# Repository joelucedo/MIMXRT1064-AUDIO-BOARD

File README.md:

# MIMXRT1064 MCU BOARD

## WHAT ?
M7 MCU + SDRAM + FLASH + SD
</br>
## STATUS
Work in progress.
</br>
## SPECS
#### MCU : MIMXRT1064CVL5B 
* ***Cores*** : 1 x ARM Cortex M7 (32KB L1 Cache - FPU)
* ***Clock frequency*** : 528 MHz  
* ***On chip Flash*** : 4MB  
* ***On chip RAM*** : 1MB
* ***USB*** : Two USB 2.0 HS OTG controllers with integrated PHY interfaces
#### SDRAM : IS42S16160J-6BLI
* ***Memory Size*** : 256Mb
* ***Data Bus Width*** : 16 Bit
* ***Maximum clock frequency*** : 166MHz
#### QSPI Flash : IS25WP064A-JBLE
* ***Memory Size*** : 64Mbit
* ***Data Bus Width*** : 8 Bit
* ***Maximum clock frequency*** : 133MHz
#### SD Memory Card Socket
* ***Capacity*** : Up to 2TB SDHX card
* ***Data transfer rate*** : Up to 104 MB/s (UHS-I SDR104)

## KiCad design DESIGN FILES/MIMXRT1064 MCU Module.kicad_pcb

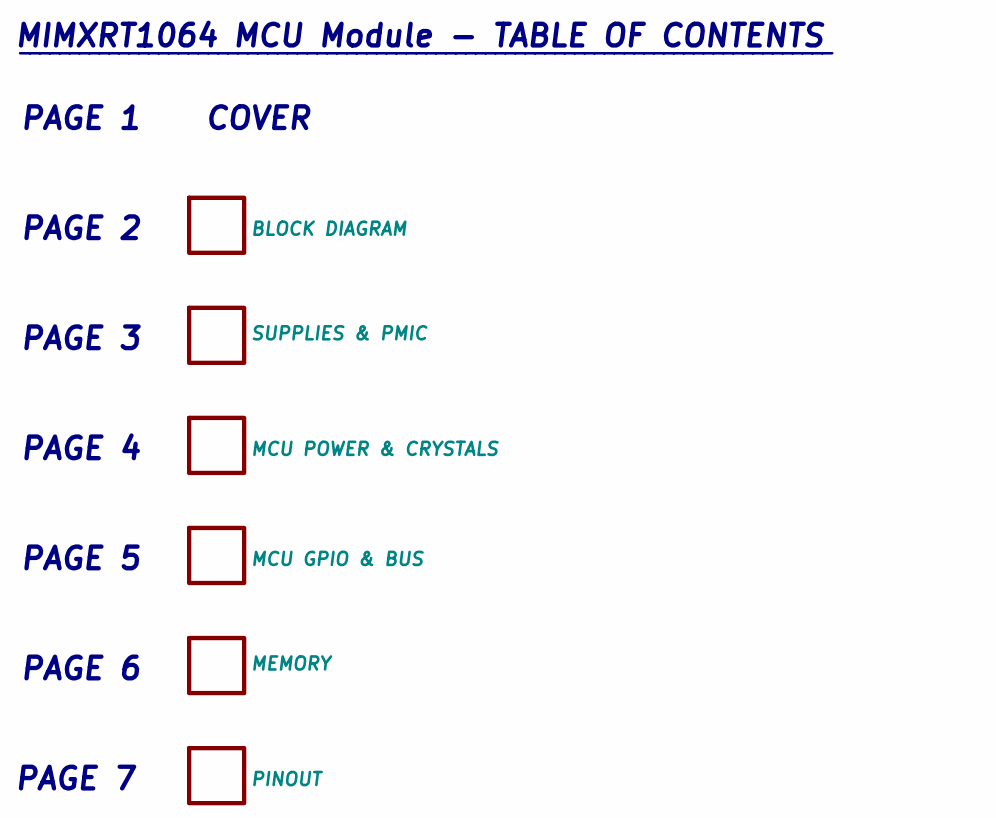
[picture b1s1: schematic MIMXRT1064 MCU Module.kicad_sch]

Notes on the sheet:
MIMXRT1064 MCU Module - TABLE OF CONTENTS
PAGE 6
PAGE 3
PAGE 4
PAGE 1 COVER
PAGE 2
PAGE 5
__________________________________________________________________________________
PAGE 7

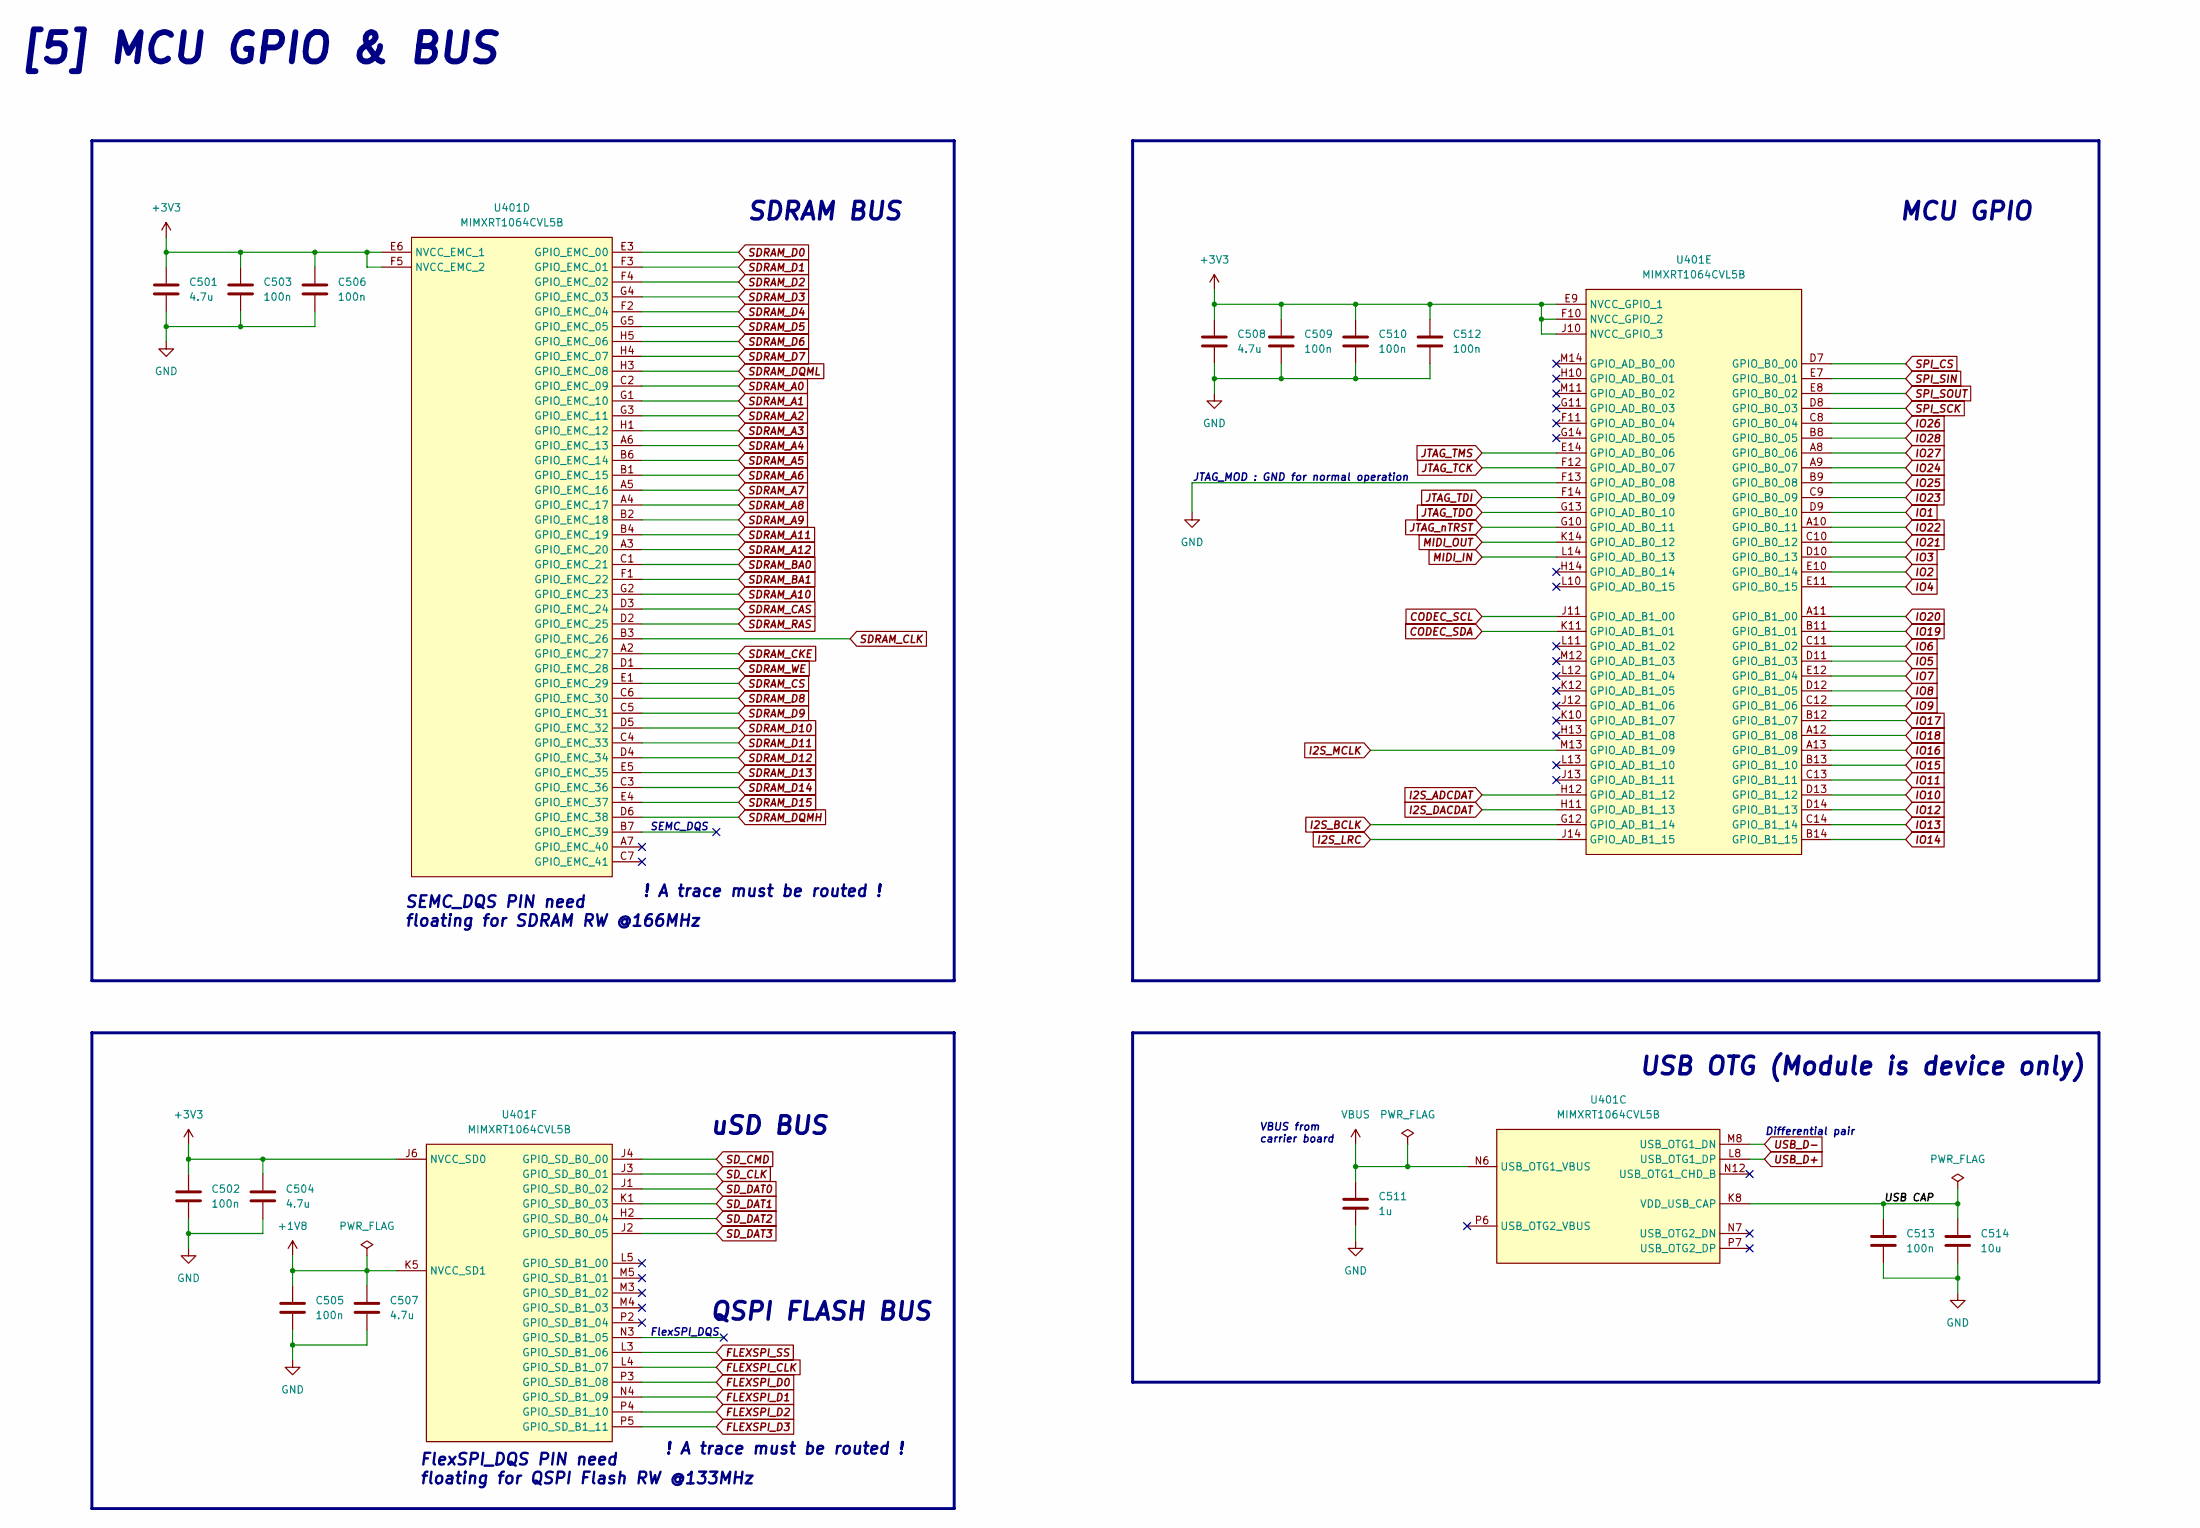
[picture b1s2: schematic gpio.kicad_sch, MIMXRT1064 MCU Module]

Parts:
C501, C504, C507, C508: 4.7u; 0402_CL05A475MP5NRNC
C502, C503, C505, C506, C509, C510, C512, C513: 100n; 0402_CL05B104KB54PNC
C511: 1u; 0402_CL05A105KA5NQNC
C514: 10u; 0603_CL10A106KP8NNNC
U401: MIMXRT1064CVL5B

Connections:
+1V8: C505.1, C507.1, U401.K5 (NVCC_SD1); also elsewhere on the board
+3V3: C501.1, C502.1, C503.1, C504.1, C506.1, C508.1, C509.1, C510.1, C512.1, U401.E6 (NVCC_EMC_1), U401.E9 (NVCC_GPIO_1), U401.F5 (NVCC_EMC_2), U401.F10 (NVCC_GPIO_2), U401.J6 (NVCC_SD0), U401.J10 (NVCC_GPIO_3); also elsewhere on the board
/MCU GPIO & BUS/USB CAP: C513.1, C514.1, U401.K8 (VDD_USB_CAP)
CODEC_SCL: U401.J11 (GPIO_AD_B1_00); also elsewhere on the board
CODEC_SDA: U401.K11 (GPIO_AD_B1_01); also elsewhere on the board
FLEXSPI_CLK: U401.L4 (GPIO_SD_B1_07); also elsewhere on the board
FLEXSPI_D0: U401.P3 (GPIO_SD_B1_08); also elsewhere on the board
FLEXSPI_D1: U401.N4 (GPIO_SD_B1_09); also elsewhere on the board
FLEXSPI_D2: U401.P4 (GPIO_SD_B1_10); also elsewhere on the board
FLEXSPI_D3: U401.P5 (GPIO_SD_B1_11); also elsewhere on the board
FLEXSPI_SS: U401.L3 (GPIO_SD_B1_06); also elsewhere on the board
GND: C501.2, C502.2, C503.2, C504.2, C505.2, C506.2, C507.2, C508.2, C509.2, C510.2, C511.2, C512.2, C513.2, C514.2, U401.F13 (GPIO_AD_B0_08); also elsewhere on the board
I2S_ADCDAT: U401.H12 (GPIO_AD_B1_12); also elsewhere on the board
I2S_BCLK: U401.G12 (GPIO_AD_B1_14); also elsewhere on the board
I2S_DACDAT: U401.H11 (GPIO_AD_B1_13); also elsewhere on the board
I2S_LRC: U401.J14 (GPIO_AD_B1_15); also elsewhere on the board
I2S_MCLK: U401.M13 (GPIO_AD_B1_09); also elsewhere on the board
IO1: U401.D9 (GPIO_B0_10); also elsewhere on the board
IO2: U401.E10 (GPIO_B0_14); also elsewhere on the board
IO3: U401.D10 (GPIO_B0_13); also elsewhere on the board
IO4: U401.E11 (GPIO_B0_15); also elsewhere on the board
IO5: U401.D11 (GPIO_B1_03); also elsewhere on the board
IO6: U401.C11 (GPIO_B1_02); also elsewhere on the board
IO7: U401.E12 (GPIO_B1_04); also elsewhere on the board
IO8: U401.D12 (GPIO_B1_05); also elsewhere on the board
IO9: U401.C12 (GPIO_B1_06); also elsewhere on the board
IO10: U401.D13 (GPIO_B1_12); also elsewhere on the board
IO11: U401.C13 (GPIO_B1_11); also elsewhere on the board
IO12: U401.D14 (GPIO_B1_13); also elsewhere on the board
IO13: U401.C14 (GPIO_B1_14); also elsewhere on the board
IO14: U401.B14 (GPIO_B1_15); also elsewhere on the board
IO15: U401.B13 (GPIO_B1_10); also elsewhere on the board
IO16: U401.A13 (GPIO_B1_09); also elsewhere on the board
IO17: U401.B12 (GPIO_B1_07); also elsewhere on the board
IO18: U401.A12 (GPIO_B1_08); also elsewhere on the board
IO19: U401.B11 (GPIO_B1_01); also elsewhere on the board
IO20: U401.A11 (GPIO_B1_00); also elsewhere on the board
IO21: U401.C10 (GPIO_B0_12); also elsewhere on the board
IO22: U401.A10 (GPIO_B0_11); also elsewhere on the board
IO23: U401.C9 (GPIO_B0_09); also elsewhere on the board
IO24: U401.A9 (GPIO_B0_07); also elsewhere on the board
IO25: U401.B9 (GPIO_B0_08); also elsewhere on the board
IO26: U401.C8 (GPIO_B0_04); also elsewhere on the board
IO27: U401.A8 (GPIO_B0_06); also elsewhere on the board
IO28: U401.B8 (GPIO_B0_05); also elsewhere on the board
JTAG_TCK: U401.F12 (GPIO_AD_B0_07); also elsewhere on the board
JTAG_TDI: U401.F14 (GPIO_AD_B0_09); also elsewhere on the board
JTAG_TDO: U401.G13 (GPIO_AD_B0_10); also elsewhere on the board
JTAG_TMS: U401.E14 (GPIO_AD_B0_06); also elsewhere on the board
JTAG_nTRST: U401.G10 (GPIO_AD_B0_11); also elsewhere on the board
MIDI_IN: U401.L14 (GPIO_AD_B0_13); also elsewhere on the board
MIDI_OUT: U401.K14 (GPIO_AD_B0_12); also elsewhere on the board
SDRAM_A0: U401.C2 (GPIO_EMC_09); also elsewhere on the board
SDRAM_A1: U401.G1 (GPIO_EMC_10); also elsewhere on the board
SDRAM_A2: U401.G3 (GPIO_EMC_11); also elsewhere on the board
SDRAM_A3: U401.H1 (GPIO_EMC_12); also elsewhere on the board
SDRAM_A4: U401.A6 (GPIO_EMC_13); also elsewhere on the board
SDRAM_A5: U401.B6 (GPIO_EMC_14); also elsewhere on the board
SDRAM_A6: U401.B1 (GPIO_EMC_15); also elsewhere on the board
SDRAM_A7: U401.A5 (GPIO_EMC_16); also elsewhere on the board
SDRAM_A8: U401.A4 (GPIO_EMC_17); also elsewhere on the board
SDRAM_A9: U401.B2 (GPIO_EMC_18); also elsewhere on the board
SDRAM_A10: U401.G2 (GPIO_EMC_23); also elsewhere on the board
SDRAM_A11: U401.B4 (GPIO_EMC_19); also elsewhere on the board
SDRAM_A12: U401.A3 (GPIO_EMC_20); also elsewhere on the board
SDRAM_BA0: U401.C1 (GPIO_EMC_21); also elsewhere on the board
SDRAM_BA1: U401.F1 (GPIO_EMC_22); also elsewhere on the board
SDRAM_CAS: U401.D3 (GPIO_EMC_24); also elsewhere on the board
SDRAM_CKE: U401.A2 (GPIO_EMC_27); also elsewhere on the board
SDRAM_CLK: U401.B3 (GPIO_EMC_26); also elsewhere on the board
SDRAM_CS: U401.E1 (GPIO_EMC_29); also elsewhere on the board
SDRAM_D0: U401.E3 (GPIO_EMC_00); also elsewhere on the board
SDRAM_D1: U401.F3 (GPIO_EMC_01); also elsewhere on the board
SDRAM_D2: U401.F4 (GPIO_EMC_02); also elsewhere on the board
SDRAM_D3: U401.G4 (GPIO_EMC_03); also elsewhere on the board
SDRAM_D4: U401.F2 (GPIO_EMC_04); also elsewhere on the board
SDRAM_D5: U401.G5 (GPIO_EMC_05); also elsewhere on the board
SDRAM_D6: U401.H5 (GPIO_EMC_06); also elsewhere on the board
SDRAM_D7: U401.H4 (GPIO_EMC_07); also elsewhere on the board
SDRAM_D8: U401.C6 (GPIO_EMC_30); also elsewhere on the board
SDRAM_D9: U401.C5 (GPIO_EMC_31); also elsewhere on the board
SDRAM_D10: U401.D5 (GPIO_EMC_32); also elsewhere on the board
SDRAM_D11: U401.C4 (GPIO_EMC_33); also elsewhere on the board
SDRAM_D12: U401.D4 (GPIO_EMC_34); also elsewhere on the board
SDRAM_D13: U401.E5 (GPIO_EMC_35); also elsewhere on the board
SDRAM_D14: U401.C3 (GPIO_EMC_36); also elsewhere on the board
SDRAM_D15: U401.E4 (GPIO_EMC_37); also elsewhere on the board
SDRAM_DQMH: U401.D6 (GPIO_EMC_38); also elsewhere on the board
SDRAM_DQML: U401.H3 (GPIO_EMC_08); also elsewhere on the board
SDRAM_RAS: U401.D2 (GPIO_EMC_25); also elsewhere on the board
SDRAM_WE: U401.D1 (GPIO_EMC_28); also elsewhere on the board
SD_CLK: U401.J3 (GPIO_SD_B0_01); also elsewhere on the board
SD_CMD: U401.J4 (GPIO_SD_B0_00); also elsewhere on the board
SD_DAT0: U401.J1 (GPIO_SD_B0_02); also elsewhere on the board
SD_DAT1: U401.K1 (GPIO_SD_B0_03); also elsewhere on the board
SD_DAT2: U401.H2 (GPIO_SD_B0_04); also elsewhere on the board
SD_DAT3: U401.J2 (GPIO_SD_B0_05); also elsewhere on the board
SPI_CS: U401.D7 (GPIO_B0_00); also elsewhere on the board
SPI_SCK: U401.D8 (GPIO_B0_03); also elsewhere on the board
SPI_SIN: U401.E7 (GPIO_B0_01); also elsewhere on the board
SPI_SOUT: U401.E8 (GPIO_B0_02); also elsewhere on the board
USB_D+: U401.L8 (USB_OTG1_DP); also elsewhere on the board
USB_D-: U401.M8 (USB_OTG1_DN); also elsewhere on the board
VBUS: C511.1, U401.N6 (USB_OTG1_VBUS); also elsewhere on the board

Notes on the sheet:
QSPI FLASH BUS
uSD BUS
SDRAM BUS
Differential pair
USB OTG (Module is device only)
FlexSPI_DQS
[5] MCU GPIO & BUS
VBUS from carrier board
SEMC_DQS
MCU GPIO
! A trace must be routed !
FlexSPI_DQS PIN need floating for QSPI Flash RW @133MHz
SEMC_DQS PIN need floating for SDRAM RW @166MHz
JTAG_MOD : GND for normal operation

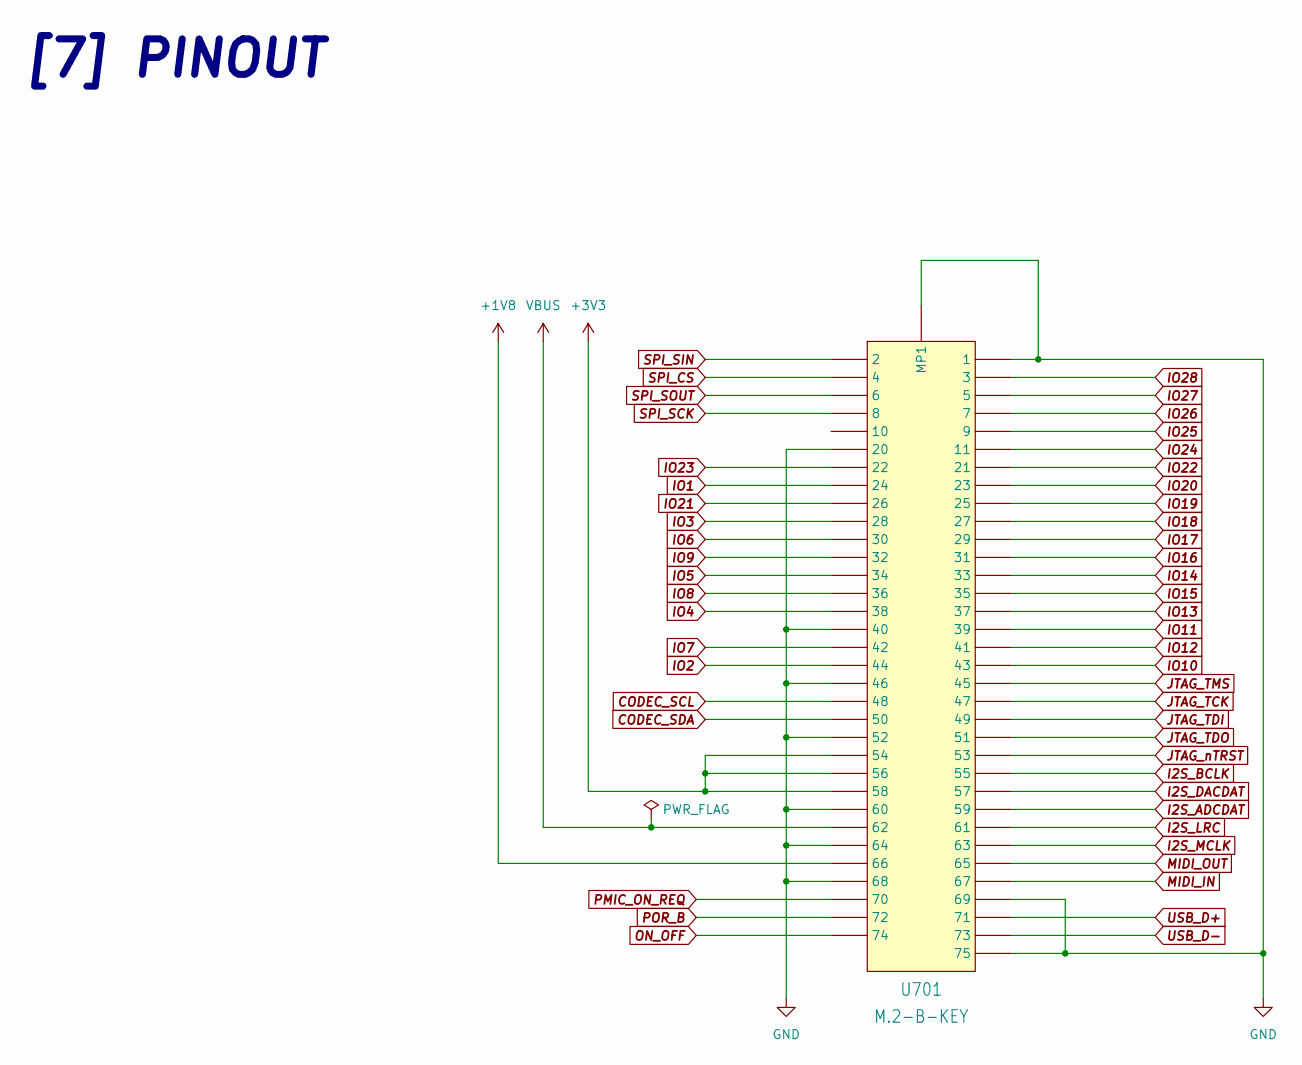
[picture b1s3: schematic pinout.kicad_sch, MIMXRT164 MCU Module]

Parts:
U701: M.2-B-KEY

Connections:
+1V8: U701.P$66 (66); also elsewhere on the board
+3V3: U701.P$54 (54), U701.P$56 (56), U701.P$58 (58); also elsewhere on the board
CODEC_SCL: U701.P$48 (48); also elsewhere on the board
CODEC_SDA: U701.P$50 (50); also elsewhere on the board
GND: U701.MOUNTING-HOLE (MP1), U701.P$1 (1), U701.P$20 (20), U701.P$40 (40), U701.P$46 (46), U701.P$52 (52), U701.P$60 (60), U701.P$64 (64), U701.P$68 (68), U701.P$69 (69), U701.P$75 (75); also elsewhere on the board
I2S_ADCDAT: U701.P$59 (59); also elsewhere on the board
I2S_BCLK: U701.P$55 (55); also elsewhere on the board
I2S_DACDAT: U701.P$57 (57); also elsewhere on the board
I2S_LRC: U701.P$61 (61); also elsewhere on the board
I2S_MCLK: U701.P$63 (63); also elsewhere on the board
IO1: U701.P$24 (24); also elsewhere on the board
IO2: U701.P$44 (44); also elsewhere on the board
IO3: U701.P$28 (28); also elsewhere on the board
IO4: U701.P$38 (38); also elsewhere on the board
IO5: U701.P$34 (34); also elsewhere on the board
IO6: U701.P$30 (30); also elsewhere on the board
IO7: U701.P$42 (42); also elsewhere on the board
IO8: U701.P$36 (36); also elsewhere on the board
IO9: U701.P$32 (32); also elsewhere on the board
IO10: U701.P$43 (43); also elsewhere on the board
IO11: U701.P$39 (39); also elsewhere on the board
IO12: U701.P$41 (41); also elsewhere on the board
IO13: U701.P$37 (37); also elsewhere on the board
IO14: U701.P$33 (33); also elsewhere on the board
IO15: U701.P$35 (35); also elsewhere on the board
IO16: U701.P$31 (31); also elsewhere on the board
IO17: U701.P$29 (29); also elsewhere on the board
IO18: U701.P$27 (27); also elsewhere on the board
IO19: U701.P$25 (25); also elsewhere on the board
IO20: U701.P$23 (23); also elsewhere on the board
IO21: U701.P$26 (26); also elsewhere on the board
IO22: U701.P$21 (21); also elsewhere on the board
IO23: U701.P$22 (22); also elsewhere on the board
IO24: U701.P$11 (11); also elsewhere on the board
IO25: U701.P$9 (9); also elsewhere on the board
IO26: U701.P$7 (7); also elsewhere on the board
IO27: U701.P$5 (5); also elsewhere on the board
IO28: U701.P$3 (3); also elsewhere on the board
JTAG_TCK: U701.P$47 (47); also elsewhere on the board
JTAG_TDI: U701.P$49 (49); also elsewhere on the board
JTAG_TDO: U701.P$51 (51); also elsewhere on the board
JTAG_TMS: U701.P$45 (45); also elsewhere on the board
JTAG_nTRST: U701.P$53 (53); also elsewhere on the board
MIDI_IN: U701.P$67 (67); also elsewhere on the board
MIDI_OUT: U701.P$65 (65); also elsewhere on the board
ON_OFF: U701.P$74 (74); also elsewhere on the board
PMIC_ON_REQ: U701.P$70 (70); also elsewhere on the board
POR_B: U701.P$72 (72); also elsewhere on the board
SPI_CS: U701.P$4 (4); also elsewhere on the board
SPI_SCK: U701.P$8 (8); also elsewhere on the board
SPI_SIN: U701.P$2 (2); also elsewhere on the board
SPI_SOUT: U701.P$6 (6); also elsewhere on the board
USB_D+: U701.P$71 (71); also elsewhere on the board
USB_D-: U701.P$73 (73); also elsewhere on the board
VBUS: U701.P$62 (62); also elsewhere on the board

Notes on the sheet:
[7] PINOUT

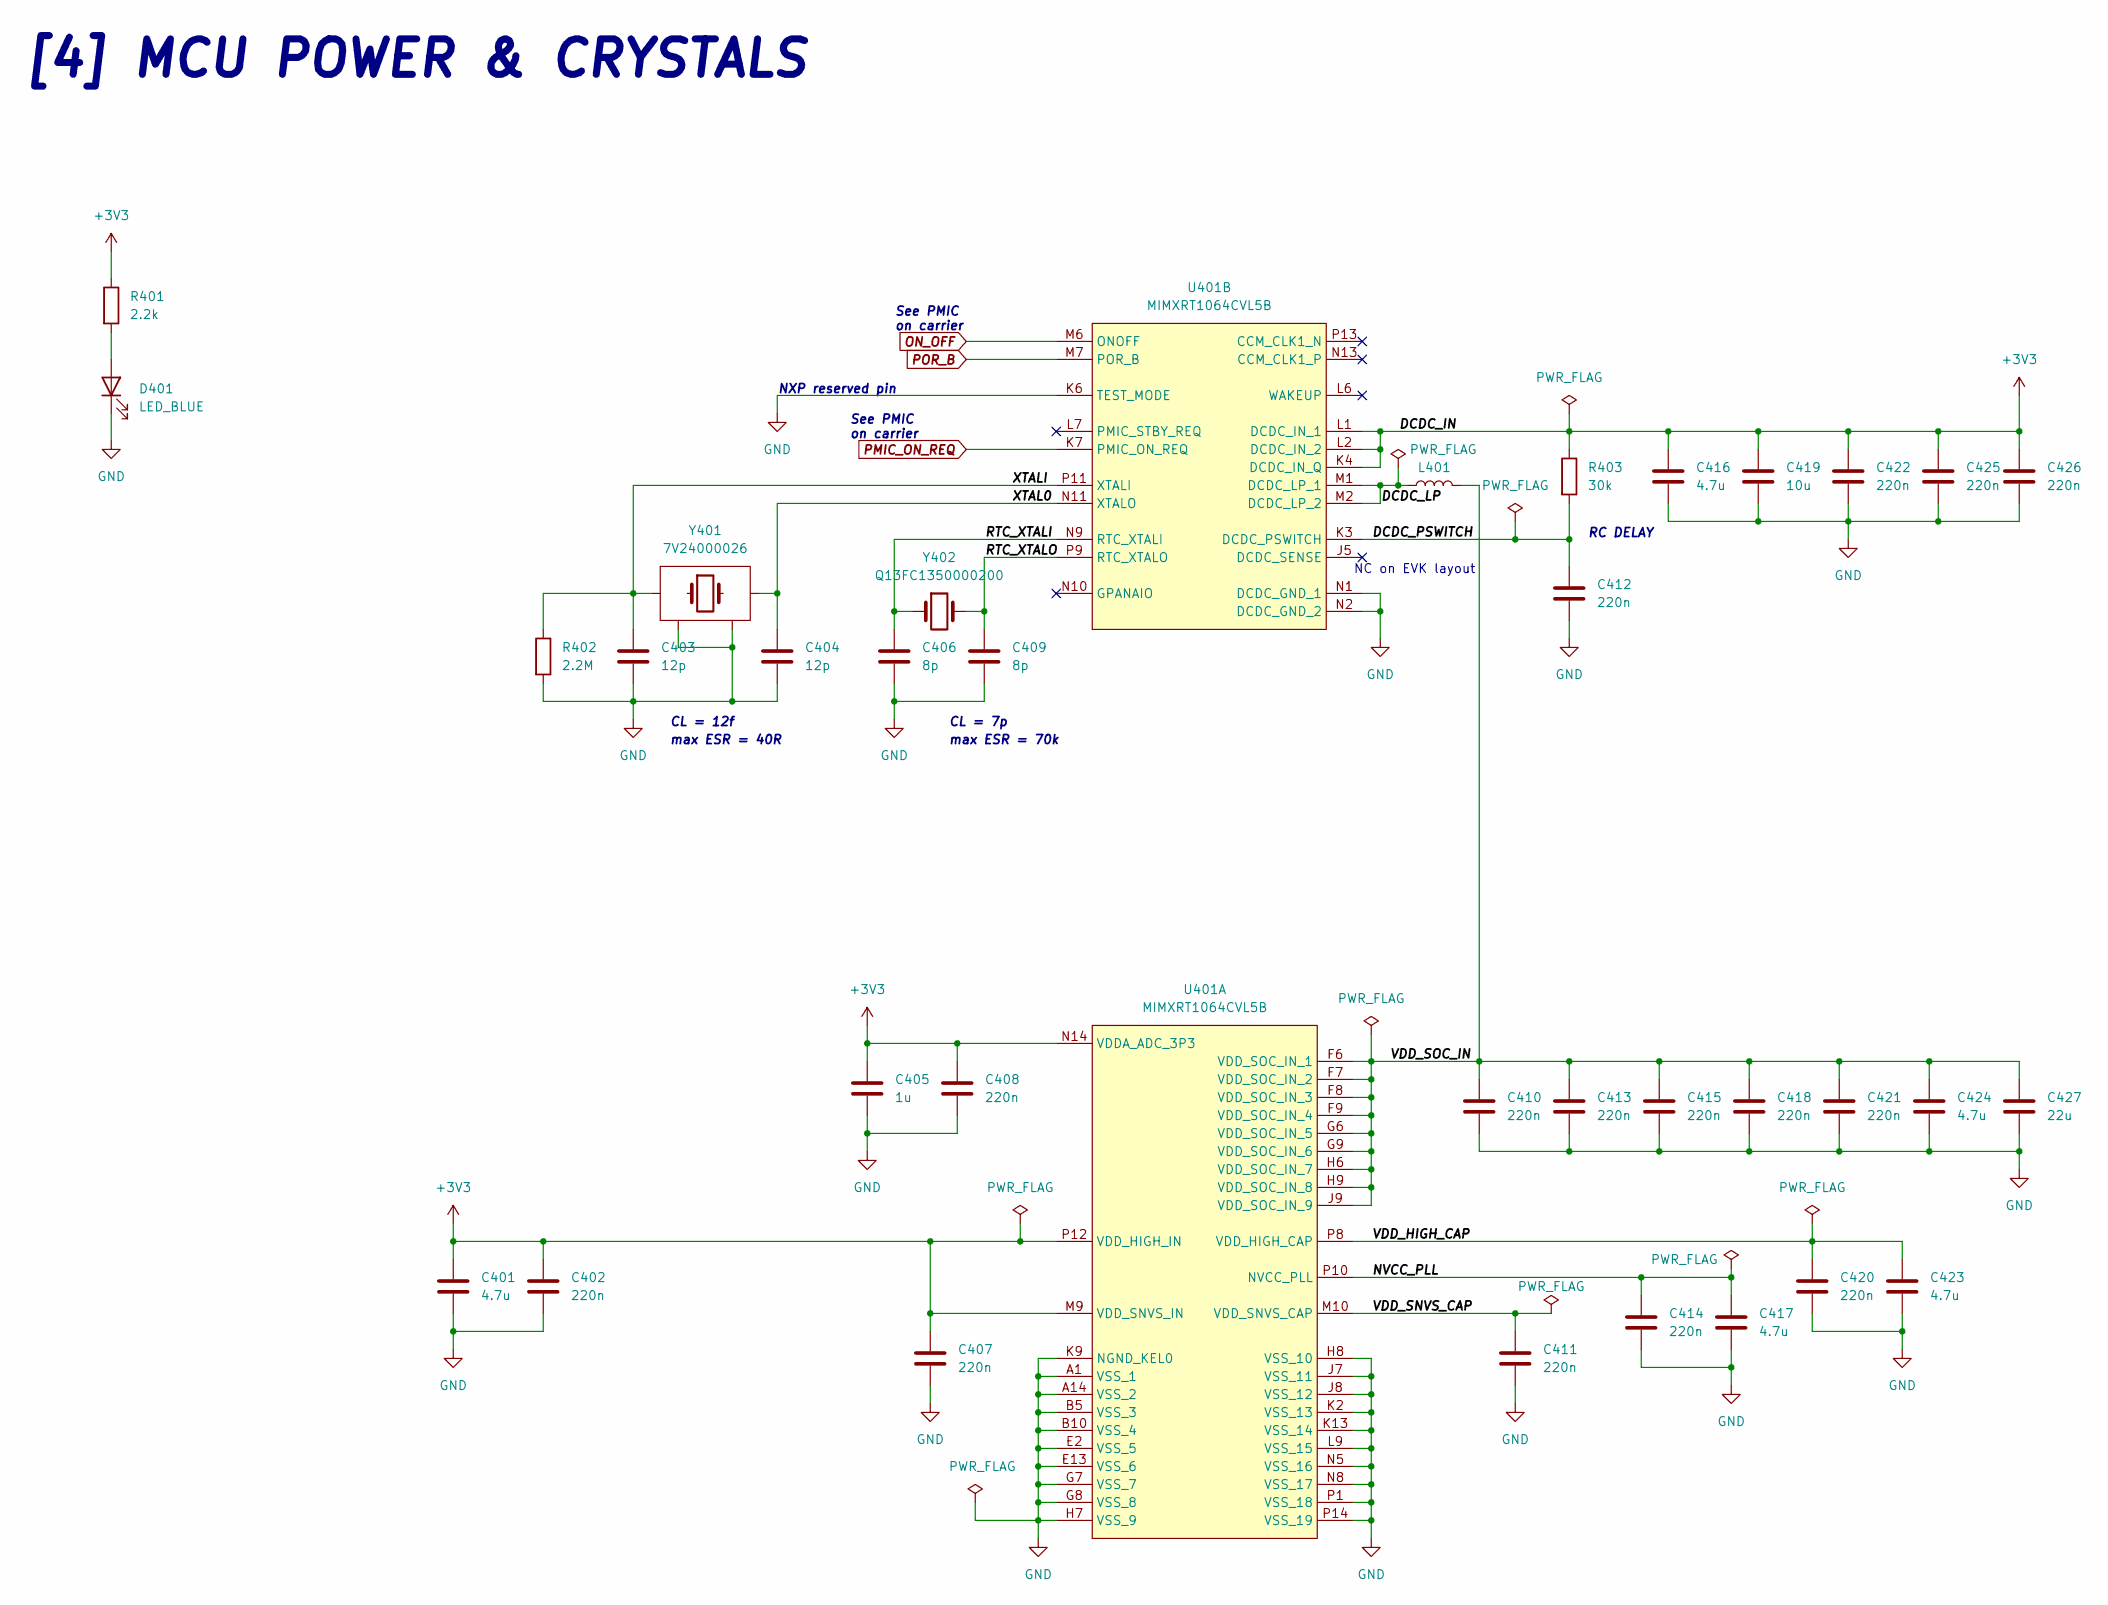
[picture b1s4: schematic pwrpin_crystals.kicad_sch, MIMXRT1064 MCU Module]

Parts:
C401, C416, C417, C423, C424: 4.7u; 0402_CL05A475MP5NRNC
C402, C407, C408, C410, C411, C412, C413, C414, C415, C418, C420, C421, C422, C425, C426: 220n; 0402_CL05B224KO5NNNC
C403, C404: 12p; CL10C120JB81PNC
C405: 1u; 0402_CL05A105KA5NQNC
C406, C409: 8p; CL10C080DB81PNC
C419: 10u; 0603_CL10A106KP8NNNC
C427: 22u; 0603_CL10A226MQ8NRNC
D401: LED_BLUE; 19-218_BHC-ZL1M2QY_3T
L401: VLS4012ET-4R7M
R401: 2.2k; 0603WAF2201T5E
R402: 2.2M; 0402WGJ0225TCE
R403: 30k; AF0402FR-0730KL
U401: MIMXRT1064CVL5B
Y401: 7V24000026
Y402: Q13FC1350000200

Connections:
+3V3: C401.1, C402.1, C405.1, C407.1, C408.1, C416.1, C419.1, C422.1, C425.1, C426.1, R401.1, R403.1, U401.K4 (DCDC_IN_Q), U401.L1 (DCDC_IN_1), U401.L2 (DCDC_IN_2), U401.M9 (VDD_SNVS_IN), U401.N14 (VDDA_ADC_3P3), U401.P12 (VDD_HIGH_IN); also elsewhere on the board
/MCU POWER & CRYSTALS/DCDC_LP: L401.1, U401.M1 (DCDC_LP_1), U401.M2 (DCDC_LP_2)
/MCU POWER & CRYSTALS/DCDC_PSWITCH: C412.1, R403.2, U401.K3 (DCDC_PSWITCH)
/MCU POWER & CRYSTALS/NVCC_PLL: C414.1, C417.1, U401.P10 (NVCC_PLL)
/MCU POWER & CRYSTALS/RTC_XTALI: C406.1, U401.N9 (RTC_XTALI), Y402.1
/MCU POWER & CRYSTALS/RTC_XTALO: C409.1, U401.P9 (RTC_XTALO), Y402.2
/MCU POWER & CRYSTALS/VDD_HIGH_CAP: C420.1, C423.1, U401.P8 (VDD_HIGH_CAP)
/MCU POWER & CRYSTALS/VDD_SNVS_CAP: C411.1, U401.M10 (VDD_SNVS_CAP)
/MCU POWER & CRYSTALS/VDD_SOC_IN: C410.1, C413.1, C415.1, C418.1, C421.1, C424.1, C427.1, L401.2, U401.F6 (VDD_SOC_IN_1), U401.F7 (VDD_SOC_IN_2), U401.F8 (VDD_SOC_IN_3), U401.F9 (VDD_SOC_IN_4), U401.G6 (VDD_SOC_IN_5), U401.G9 (VDD_SOC_IN_6), U401.H6 (VDD_SOC_IN_7), U401.H9 (VDD_SOC_IN_8), U401.J9 (VDD_SOC_IN_9)
/MCU POWER & CRYSTALS/XTAL0: C404.1, U401.N11 (XTALO), Y401.3
/MCU POWER & CRYSTALS/XTALI: C403.1, R402.1, U401.P11 (XTALI), Y401.1
GND: C401.2, C402.2, C403.2, C404.2, C405.2, C406.2, C407.2, C408.2, C409.2, C410.2, C411.2, C412.2, C413.2, C414.2, C415.2, C416.2, C417.2, C418.2, C419.2, C420.2, C421.2, C422.2, C423.2, C424.2, C425.2, C426.2, C427.2, D401.1 (K), R402.2, U401.A1 (VSS_1), U401.A14 (VSS_2), U401.B5 (VSS_3), U401.B10 (VSS_4), U401.E2 (VSS_5), U401.E13 (VSS_6), U401.G7 (VSS_7), U401.G8 (VSS_8), U401.H7 (VSS_9), U401.H8 (VSS_10), U401.J7 (VSS_11), U401.J8 (VSS_12), U401.K2 (VSS_13), U401.K6 (TEST_MODE), U401.K9 (NGND_KEL0), U401.K13 (VSS_14), U401.L9 (VSS_15), U401.N1 (DCDC_GND_1), U401.N2 (DCDC_GND_2), U401.N5 (VSS_16), U401.N8 (VSS_17), U401.P1 (VSS_18), U401.P14 (VSS_19), Y401.2 (GND), Y401.4 (GND); also elsewhere on the board
unnamed: D401.2 (A), R401.2
ON_OFF: U401.M6 (ONOFF); also elsewhere on the board
PMIC_ON_REQ: U401.K7 (PMIC_ON_REQ); also elsewhere on the board
POR_B: U401.M7 (POR_B); also elsewhere on the board

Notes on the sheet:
RC DELAY
NC on EVK layout
[4] MCU POWER & CRYSTALS
See PMIC on carrier
CL = 7p
max ESR = 70k
CL = 12f
NXP reserved pin
max ESR = 40R

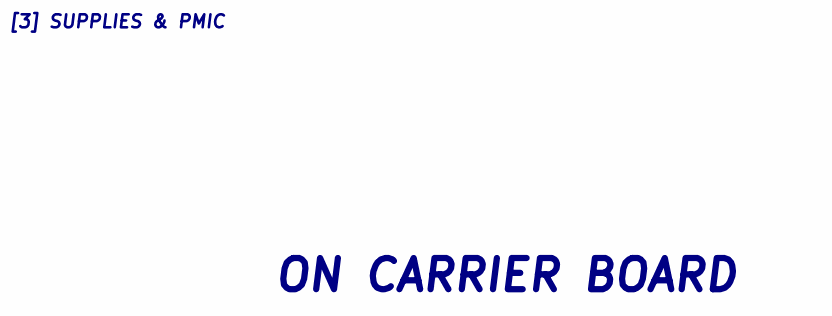
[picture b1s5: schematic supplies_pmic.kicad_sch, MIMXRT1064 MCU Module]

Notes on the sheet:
[3] SUPPLIES & PMIC
ON CARRIER BOARD
